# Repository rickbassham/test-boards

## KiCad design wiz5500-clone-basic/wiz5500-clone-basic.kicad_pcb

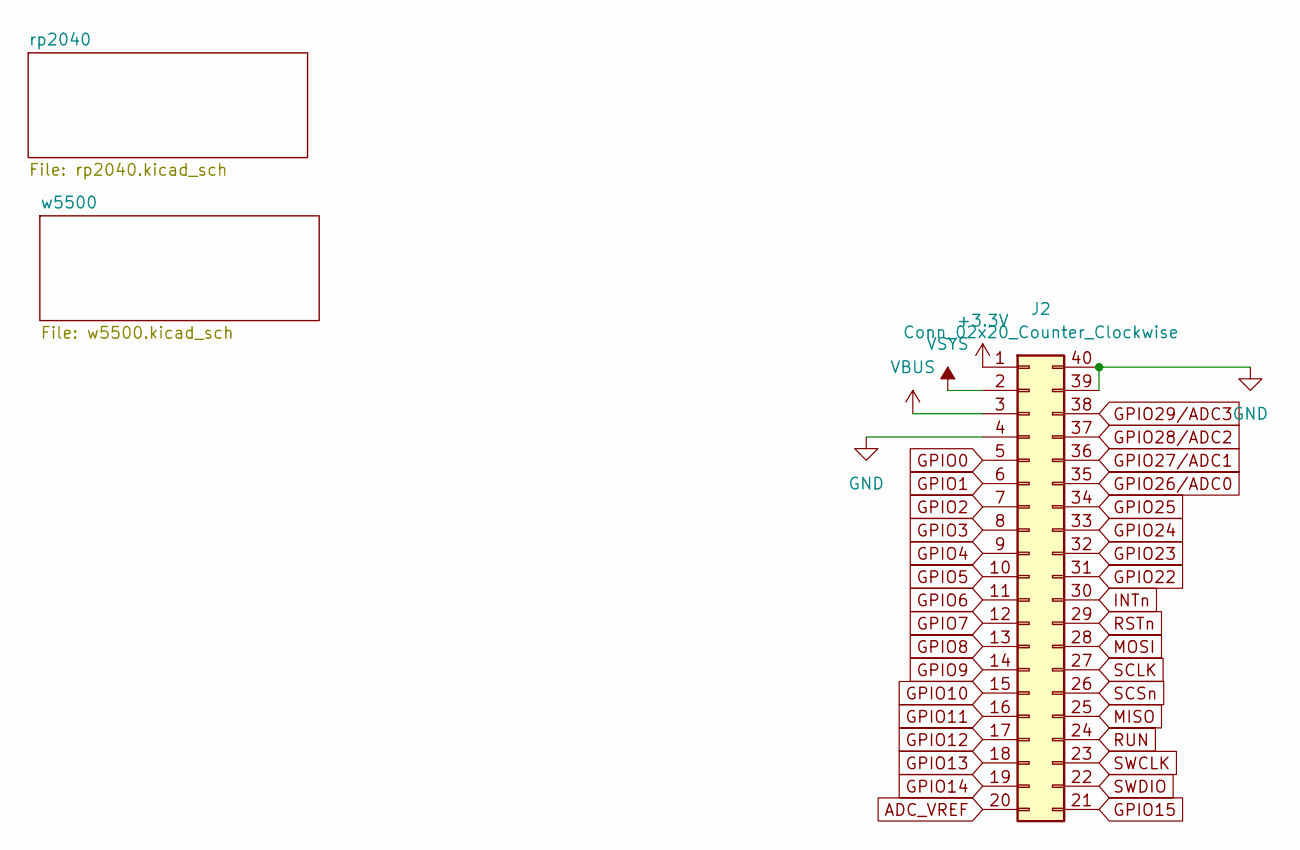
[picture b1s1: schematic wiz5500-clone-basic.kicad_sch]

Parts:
J2: Conn_02x20_Counter_Clockwise; PinHeader_2x20_P2.54mm_Vertical

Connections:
+3V3: J2.1; also elsewhere on the board
ADC_VREF: J2.20; also elsewhere on the board
GND: J2.4, J2.39, J2.40; also elsewhere on the board
GPIO0: J2.5; also elsewhere on the board
GPIO1: J2.6; also elsewhere on the board
GPIO2: J2.7; also elsewhere on the board
GPIO3: J2.8; also elsewhere on the board
GPIO4: J2.9; also elsewhere on the board
GPIO5: J2.10; also elsewhere on the board
GPIO6: J2.11; also elsewhere on the board
GPIO7: J2.12; also elsewhere on the board
GPIO8: J2.13; also elsewhere on the board
GPIO9: J2.14; also elsewhere on the board
GPIO10: J2.15; also elsewhere on the board
GPIO11: J2.16; also elsewhere on the board
GPIO12: J2.17; also elsewhere on the board
GPIO13: J2.18; also elsewhere on the board
GPIO14: J2.19; also elsewhere on the board
GPIO15: J2.21; also elsewhere on the board
GPIO22: J2.31; also elsewhere on the board
GPIO23: J2.32; also elsewhere on the board
GPIO24: J2.33; also elsewhere on the board
GPIO25: J2.34; also elsewhere on the board
GPIO26/ADC0: J2.35; also elsewhere on the board
GPIO27/ADC1: J2.36; also elsewhere on the board
GPIO28/ADC2: J2.37; also elsewhere on the board
GPIO29/ADC3: J2.38; also elsewhere on the board
INTn: J2.30; also elsewhere on the board
MISO: J2.25; also elsewhere on the board
MOSI: J2.28; also elsewhere on the board
RSTn: J2.29; also elsewhere on the board
RUN: J2.24; also elsewhere on the board
SCLK: J2.27; also elsewhere on the board
SCSn: J2.26; also elsewhere on the board
SWCLK: J2.23; also elsewhere on the board
SWDIO: J2.22; also elsewhere on the board
VBUS: J2.3; also elsewhere on the board
VSYS: J2.2; also elsewhere on the board

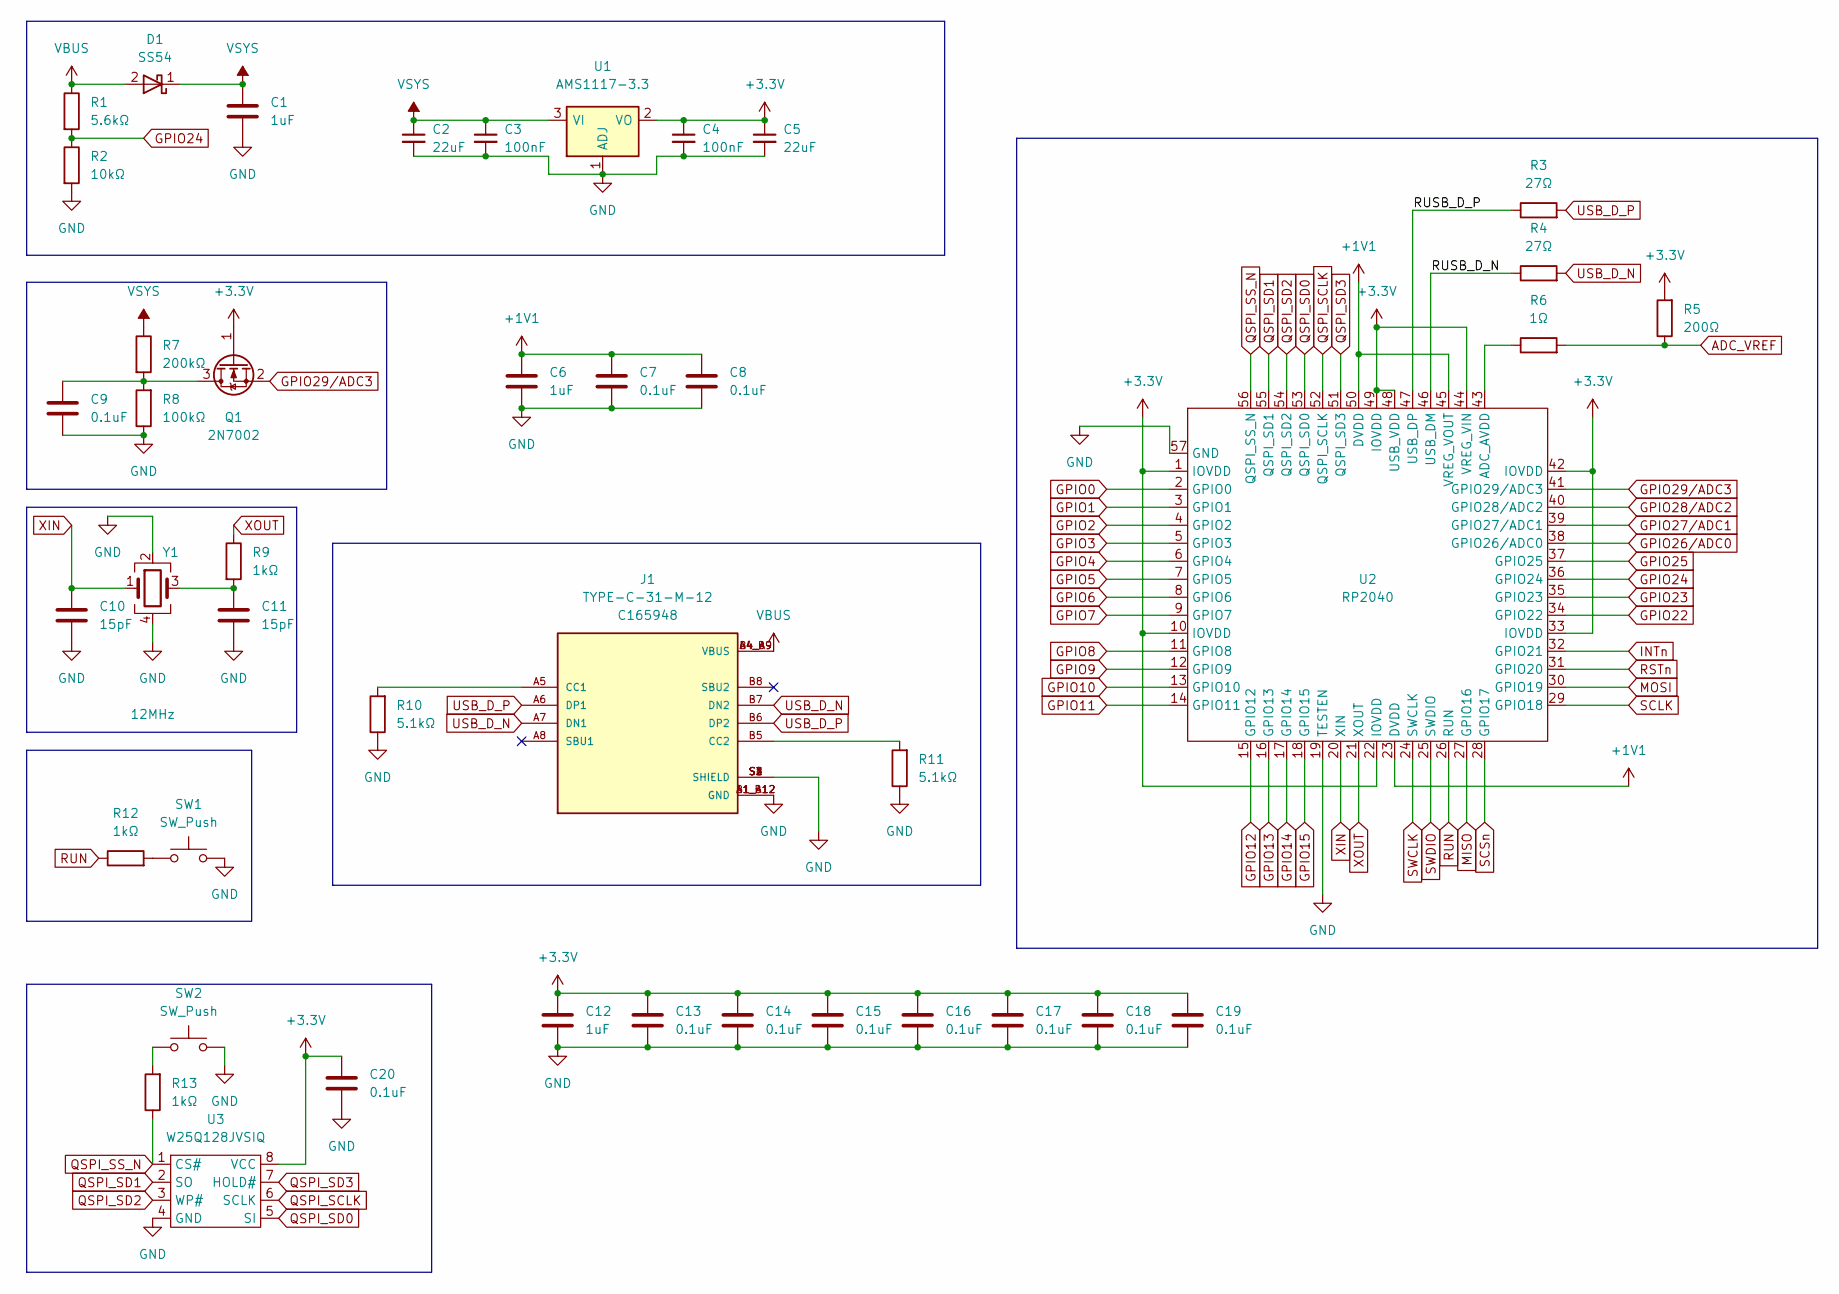
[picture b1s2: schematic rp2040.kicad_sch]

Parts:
C1, C6, C12: 1uF; C_0402_1005Metric; LCSC C52923
C2, C5: 22uF; C_0805_2012Metric; LCSC C45783
C3, C4: 100nF; C_0402_1005Metric; LCSC C307331
C7, C8, C9, C13, C14, C15, C16, C17, C18, C19, C20: 0.1uF; C_0402_1005Metric; LCSC C1525
C10, C11: 15pF; C_0402_1005Metric; LCSC C1548
D1: SS54; D_SMA; LCSC C22452
J1: TYPE-C-31-M-12; HRO_TYPE-C-31-M-12; LCSC C165948
Q1: 2N7002; SOT-23; LCSC C8545
R1: 5.6kΩ; R_0402_1005Metric; LCSC C25908
R2: 10kΩ; R_0402_1005Metric; LCSC C25744
R3, R4: 27Ω; R_0603_1608Metric; LCSC C25190
R5: 200Ω; R_0402_1005Metric; LCSC C25087
R6: 1Ω; R_0402_1005Metric; LCSC C25086
R7: 200kΩ; R_0402_1005Metric; LCSC C25764
R8: 100kΩ; R_0402_1005Metric; LCSC C25741
R9, R12, R13: 1kΩ; R_0402_1005Metric; LCSC C11702
R10, R11: 5.1kΩ; R_0402_1005Metric; LCSC C25905
SW1, SW2: SW_Push; SW_TS-1187A-B-A-B; LCSC C318884
U1: AMS1117-3.3; SOT-223-3_TabPin2; LCSC C6186
U2: RP2040; LCSC C2040
U3: W25Q128JVSIQ; SOIC-8_5.23x5.23mm_P1.27mm; LCSC C97521
Y1: 12MHz; Crystal_SMD_3225-4Pin_3.2x2.5mm; LCSC C9002

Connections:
+1V1: C6.1, C7.1, C8.1, U2.23 (DVDD), U2.45 (VREG_VOUT), U2.50 (DVDD)
+3V3: C4.1, C5.1, C12.1, C13.1, C14.1, C15.1, C16.1, C17.1, C18.1, C19.1, C20.1, Q1.1 (G), R5.2, U1.2 (VO), U2.1 (IOVDD), U2.10 (IOVDD), U2.22 (IOVDD), U2.33 (IOVDD), U2.42 (IOVDD), U2.44 (VREG_VIN), U2.48 (USB_VDD), U2.49 (IOVDD), U3.8 (VCC); also elsewhere on the board
/rp2040/RUSB_D_N: R4.1, U2.46 (USB_DM)
/rp2040/RUSB_D_P: R3.1, U2.47 (USB_DP)
ADC_VREF: R5.1, R6.2; also elsewhere on the board
GND: C1.2, C2.2, C3.2, C4.2, C5.2, C6.2, C7.2, C8.2, C9.2, C10.2, C11.2, C12.2, C13.2, C14.2, C15.2, C16.2, C17.2, C18.2, C19.2, C20.2, J1.A1_B12 (GND), J1.B1_A12 (GND), J1.S1 (SHIELD), J1.S2 (SHIELD), J1.S3 (SHIELD), J1.S4 (SHIELD), R2.2, R8.1, R10.1, R11.1, SW1.2, SW2.2, U1.1 (ADJ), U2.19 (TESTEN), U2.57 (GND), U3.4 (GND), Y1.2, Y1.4; also elsewhere on the board
GPIO0: U2.2 (GPIO0); also elsewhere on the board
GPIO1: U2.3 (GPIO1); also elsewhere on the board
GPIO2: U2.4 (GPIO2); also elsewhere on the board
GPIO3: U2.5 (GPIO3); also elsewhere on the board
GPIO4: U2.6 (GPIO4); also elsewhere on the board
GPIO5: U2.7 (GPIO5); also elsewhere on the board
GPIO6: U2.8 (GPIO6); also elsewhere on the board
GPIO7: U2.9 (GPIO7); also elsewhere on the board
GPIO8: U2.11 (GPIO8); also elsewhere on the board
GPIO9: U2.12 (GPIO9); also elsewhere on the board
GPIO10: U2.13 (GPIO10); also elsewhere on the board
GPIO11: U2.14 (GPIO11); also elsewhere on the board
GPIO12: U2.15 (GPIO12); also elsewhere on the board
GPIO13: U2.16 (GPIO13); also elsewhere on the board
GPIO14: U2.17 (GPIO14); also elsewhere on the board
GPIO15: U2.18 (GPIO15); also elsewhere on the board
GPIO22: U2.34 (GPIO22); also elsewhere on the board
GPIO23: U2.35 (GPIO23); also elsewhere on the board
GPIO24: R1.2, R2.1, U2.36 (GPIO24); also elsewhere on the board
GPIO25: U2.37 (GPIO25); also elsewhere on the board
GPIO26/ADC0: U2.38 (GPIO26/ADC0); also elsewhere on the board
GPIO27/ADC1: U2.39 (GPIO27/ADC1); also elsewhere on the board
GPIO28/ADC2: U2.40 (GPIO28/ADC2); also elsewhere on the board
GPIO29/ADC3: Q1.2 (S), U2.41 (GPIO29/ADC3); also elsewhere on the board
INTn: U2.32 (GPIO21); also elsewhere on the board
MISO: U2.27 (GPIO16); also elsewhere on the board
MOSI: U2.30 (GPIO19); also elsewhere on the board
unnamed: C9.1, Q1.3 (D), R7.2, R8.2
unnamed: C11.1, R9.2, Y1.3
unnamed: J1.A5 (CC1), R10.2
unnamed: J1.B5 (CC2), R11.2
unnamed: R6.1, U2.43 (ADC_AVDD)
unnamed: R12.2, SW1.1
unnamed: R13.2, SW2.1
QSPI_SCLK: U2.52 (QSPI_SCLK), U3.6 (SCLK)
QSPI_SD0: U2.53 (QSPI_SD0), U3.5 (SI)
QSPI_SD1: U2.55 (QSPI_SD1), U3.2 (SO)
QSPI_SD2: U2.54 (QSPI_SD2), U3.3 (WP#)
QSPI_SD3: U2.51 (QSPI_SD3), U3.7 (HOLD#)
QSPI_SS_N: R13.1, U2.56 (QSPI_SS_N), U3.1 (CS#)
RSTn: U2.31 (GPIO20); also elsewhere on the board
RUN: R12.1, U2.26 (RUN); also elsewhere on the board
SCLK: U2.29 (GPIO18); also elsewhere on the board
SCSn: U2.28 (GPIO17); also elsewhere on the board
SWCLK: U2.24 (SWCLK); also elsewhere on the board
SWDIO: U2.25 (SWDIO); also elsewhere on the board
USB_D_N: J1.A7 (DN1), J1.B7 (DN2), R4.2
USB_D_P: J1.A6 (DP1), J1.B6 (DP2), R3.2
VBUS: D1.2 (A), J1.A4_B9 (VBUS), J1.B4_A9 (VBUS), R1.1; also elsewhere on the board
VSYS: C1.1, C2.1, C3.1, D1.1 (K), R7.1, U1.3 (VI); also elsewhere on the board
XIN: C10.1, U2.20 (XIN), Y1.1
XOUT: R9.1, U2.21 (XOUT)

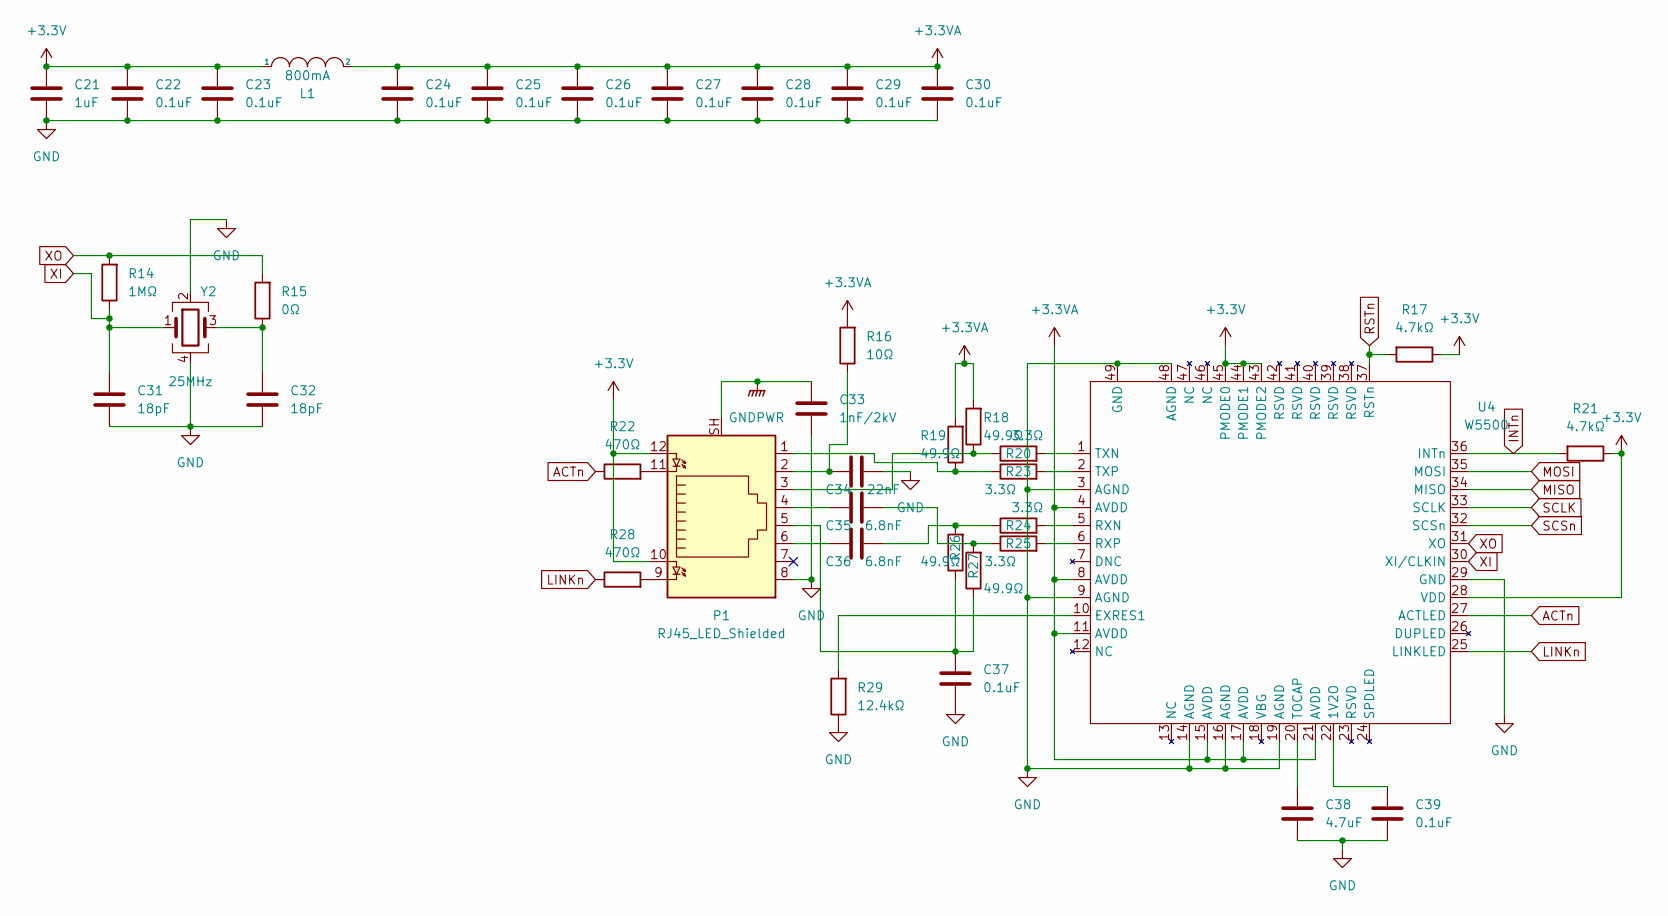
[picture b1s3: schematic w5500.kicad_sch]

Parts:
C21: 1uF; C_0402_1005Metric; LCSC C52923
C22, C23, C24, C25, C26, C27, C28, C29, C30, C37, C39: 0.1uF; C_0402_1005Metric; LCSC C1525
C31, C32: 18pF; C_0402_1005Metric; LCSC C1549
C33: 1nF/2kV; C_1206_3216Metric; LCSC C9196
C34: 22nF; C_0402_1005Metric; LCSC C1532
C35, C36: 6.8nF; C_0402_1005Metric; LCSC C1542
C38: 4.7uF; C_0402_1005Metric; LCSC C23733
L1: 800mA; L_0805_2012Metric; LCSC C1015
P1: RJ45_LED_Shielded; J1B1211CCD; Manufacturer PN J1B1211CCD; LCSC C910371
R14: 1MΩ; R_0402_1005Metric; LCSC C26083
R15: 0Ω; R_0402_1005Metric; LCSC C17168
R16: 10Ω; R_0402_1005Metric; LCSC C25077
R17, R21: 4.7kΩ; R_0402_1005Metric; LCSC C25900
R18, R19, R26, R27: 49.9Ω; R_0402_1005Metric; LCSC C25120
R20, R23, R24, R25: 3.3Ω; R_0402_1005Metric; LCSC C269403
R22, R28: 470Ω; R_0402_1005Metric; LCSC C25117
R29: 12.4kΩ; R_0402_1005Metric; LCSC C11692
U4: W5500; LQFP-48-1EP_7x7mm_P0.5mm_EP3.6x3.6mm; LCSC C32843
Y2: 25MHz; Crystal_SMD_3225-4Pin_3.2x2.5mm; LCSC C9006

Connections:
+3.3VA: C24.1, C25.1, C26.1, C27.1, C28.1, C29.1, C30.1, L1.2, R16.2, R18.2, R19.2, U4.4 (AVDD), U4.8 (AVDD), U4.11 (AVDD), U4.15 (AVDD), U4.17 (AVDD), U4.21 (AVDD)
+3V3: C21.1, C22.1, C23.1, L1.1, P1.10, P1.12, R17.1, R21.1, U4.28 (VDD), U4.43 (PMODE2), U4.44 (PMODE1), U4.45 (PMODE0); also elsewhere on the board
ACTn: R22.1, U4.27 (ACTLED)
GND: C21.2, C22.2, C23.2, C24.2, C25.2, C26.2, C27.2, C28.2, C29.2, C30.2, C31.2, C32.2, C33.2, C34.2, C37.2, C38.2, C39.2, P1.8, R29.1, U4.3 (AGND), U4.9 (AGND), U4.14 (AGND), U4.16 (AGND), U4.19 (AGND), U4.29 (GND), U4.48 (AGND), U4.49 (GND), Y2.2, Y2.4; also elsewhere on the board
GNDPWR: C33.1, P1.SH
INTn: R21.2, U4.36 (INTn); also elsewhere on the board
LINKn: R28.1, U4.25 (LINKLED)
MISO: U4.34 (MISO); also elsewhere on the board
MOSI: U4.35 (MOSI); also elsewhere on the board
unnamed: C32.1, R15.1, Y2.3
unnamed: C34.1, P1.2, R16.1
unnamed: C35.1, P1.4
unnamed: C35.2, R25.1, R27.2
unnamed: C36.1, P1.6
unnamed: C36.2, R24.1, R26.2
unnamed: C37.1, P1.5, R26.1, R27.1
unnamed: C38.1, U4.20 (TOCAP)
unnamed: C39.1, U4.22 (1V2O)
unnamed: P1.1, R19.1, R23.1
unnamed: P1.3, R18.1, R20.1
unnamed: P1.9, R28.2
unnamed: P1.11, R22.2
unnamed: R20.2, U4.1 (TXN)
unnamed: R23.2, U4.2 (TXP)
unnamed: R24.2, U4.5 (RXN)
unnamed: R25.2, U4.6 (RXP)
unnamed: R29.2, U4.10 (EXRES1)
RSTn: R17.2, U4.37 (RSTn); also elsewhere on the board
SCLK: U4.33 (SCLK); also elsewhere on the board
SCSn: U4.32 (SCSn); also elsewhere on the board
XI: C31.1, R14.1, U4.30 (XI/CLKIN), Y2.1
XO: R14.2, R15.2, U4.31 (XO)

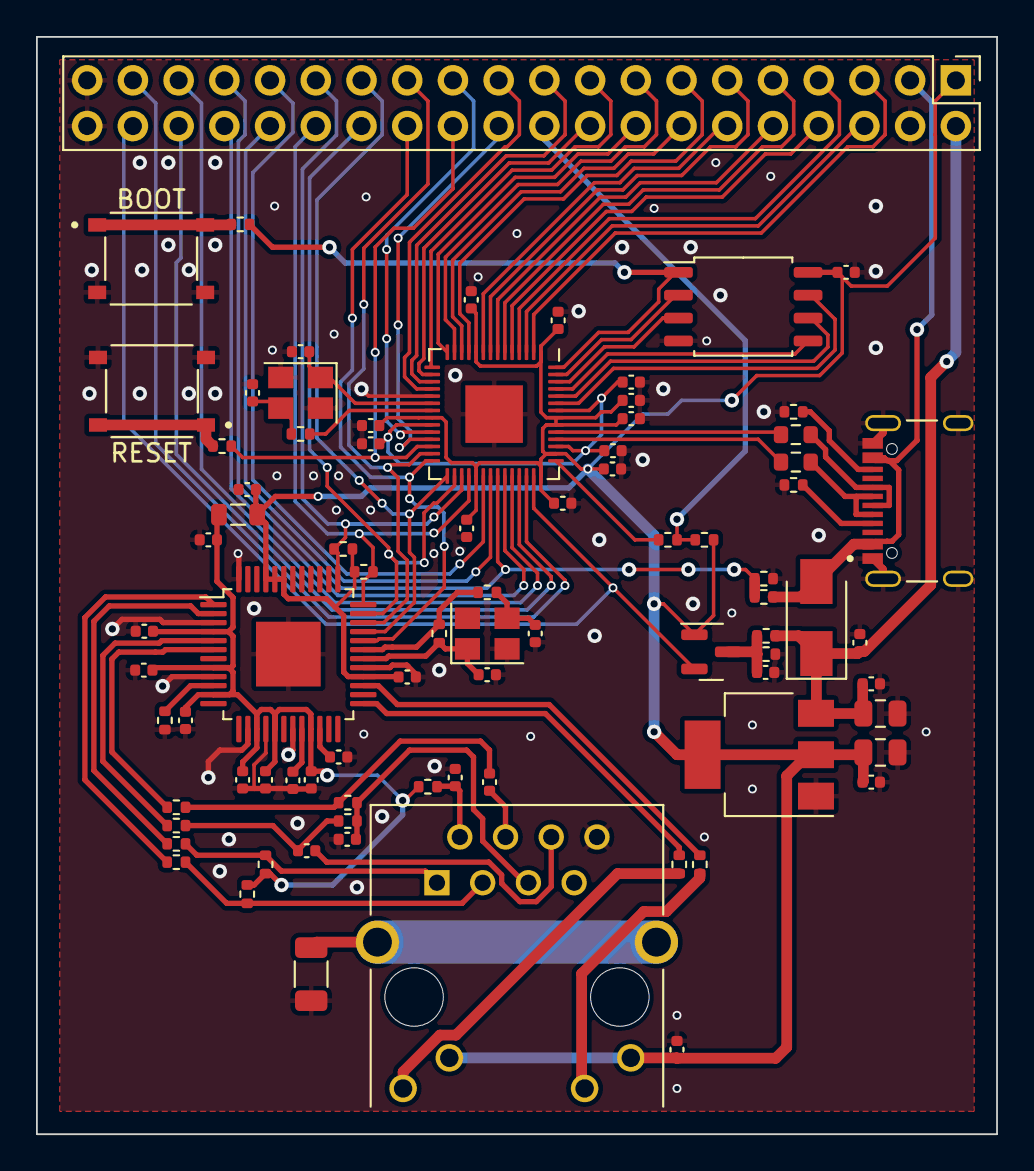
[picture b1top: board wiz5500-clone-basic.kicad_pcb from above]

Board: 2 copper layers, 53.3 x 61.0 mm, 82 parts (0 on the bottom side), 82 nets.

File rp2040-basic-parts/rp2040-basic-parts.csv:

"Designator","JLCPCB Part #","Comment","Footprint"
"C1, C6, C12, ","C52923","1uF","Capacitor_SMD:C_0402_1005Metric"
"C2, C5, ","C45783","22uF","Capacitor_SMD:C_0805_2012Metric"
"C3, C4, ","C307331","100nF","Capacitor_SMD:C_0402_1005Metric"
"C7, C8, C9, C13, C14, C15, C16, C17, C18, C19, C20, ","C1525","0.1uF","Capacitor_SMD:C_0402_1005Metric"
"C10, C11, ","C1548","15pF","Capacitor_SMD:C_0402_1005Metric"
"D1, ","C22452","SS54","Diode_SMD:D_SMA"
"J1, ","C165948","TYPE-C-31-M-12","01-rickbassham:HRO_TYPE-C-31-M-12"
"J2, J3, ","","Conn_01x20","Connector_PinHeader_2.54mm:PinHeader_1x20_P2.54mm_Vertical"
"JP1, ","","Boot_Mode","Connector_PinHeader_2.54mm:PinHeader_1x03_P2.54mm_Vertical"
"Q1, ","C8545","2N7002","Package_TO_SOT_SMD:SOT-23"
"R1, ","C25908","5.6kΩ","Resistor_SMD:R_0402_1005Metric"
"R2, ","C25744","10kΩ","Resistor_SMD:R_0402_1005Metric"
"R3, R4, ","C25190","27Ω","Resistor_SMD:R_0603_1608Metric"
"R5, ","C25087","200Ω","Resistor_SMD:R_0402_1005Metric"
"R6, ","C25086","1Ω","Resistor_SMD:R_0402_1005Metric"
"R7, ","C25764","200kΩ","Resistor_SMD:R_0402_1005Metric"
"R8, ","C25741","100kΩ","Resistor_SMD:R_0402_1005Metric"
"R9, R10, R11, ","C11702","1kΩ","Resistor_SMD:R_0402_1005Metric"
"R12, R13, ","","5.1kΩ","Resistor_SMD:R_0402_1005Metric"
"R14, ","","1MΩ","Resistor_SMD:R_0402_1005Metric"
"SW1, ","C318884","SW_Push","01-rickbassham:SW_TS-1187A-B-A-B"
"U1, ","C6186","AMS1117-3.3","Package_TO_SOT_SMD:SOT-223-3_TabPin2"
"U2, ","C9002","X322512MSB4SI","Crystal:Crystal_SMD_3225-4Pin_3.2x2.5mm"
"U3, ","C2040","RP2040","01-rickbassham:RP2040"
"U4, ","C97521","W25Q128JVSIQ","Package_SO:SOIC-8_3.9x4.9mm_P1.27mm"

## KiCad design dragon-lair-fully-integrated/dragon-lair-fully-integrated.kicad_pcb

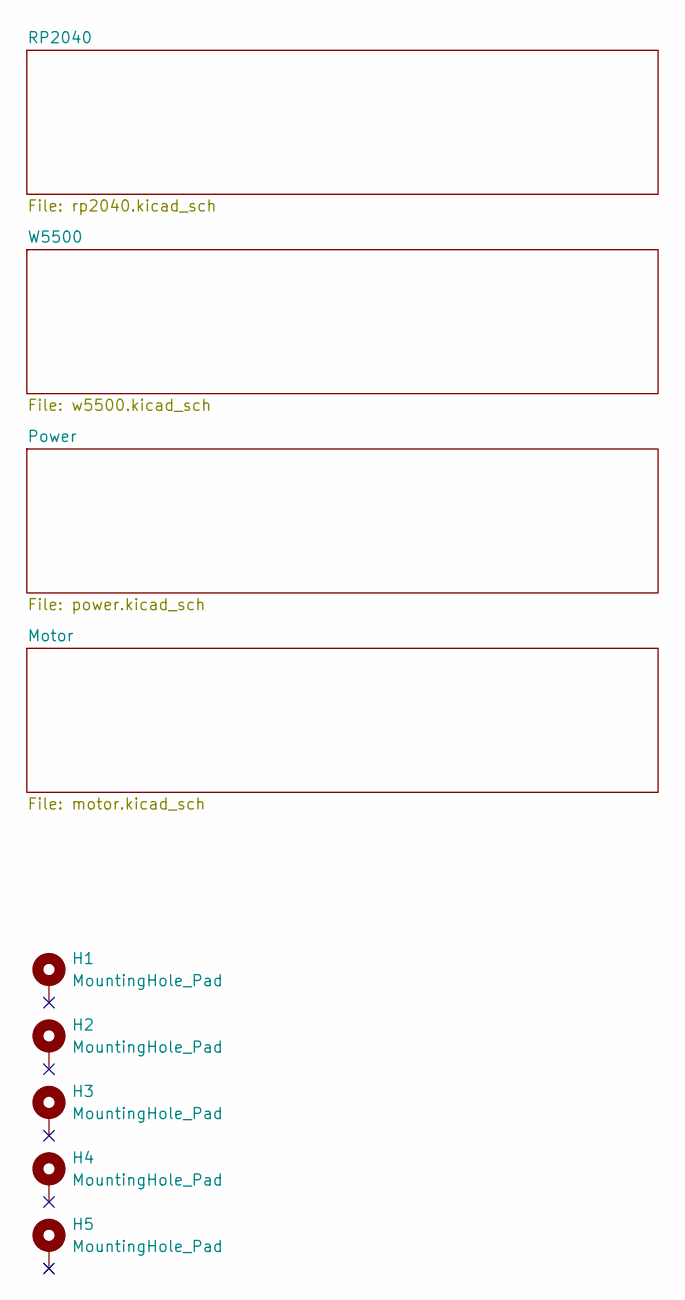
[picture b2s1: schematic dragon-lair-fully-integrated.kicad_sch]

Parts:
H1, H2, H3, H4, H5: MountingHole_Pad; MountingHole_3.2mm_M3_DIN965_Pad

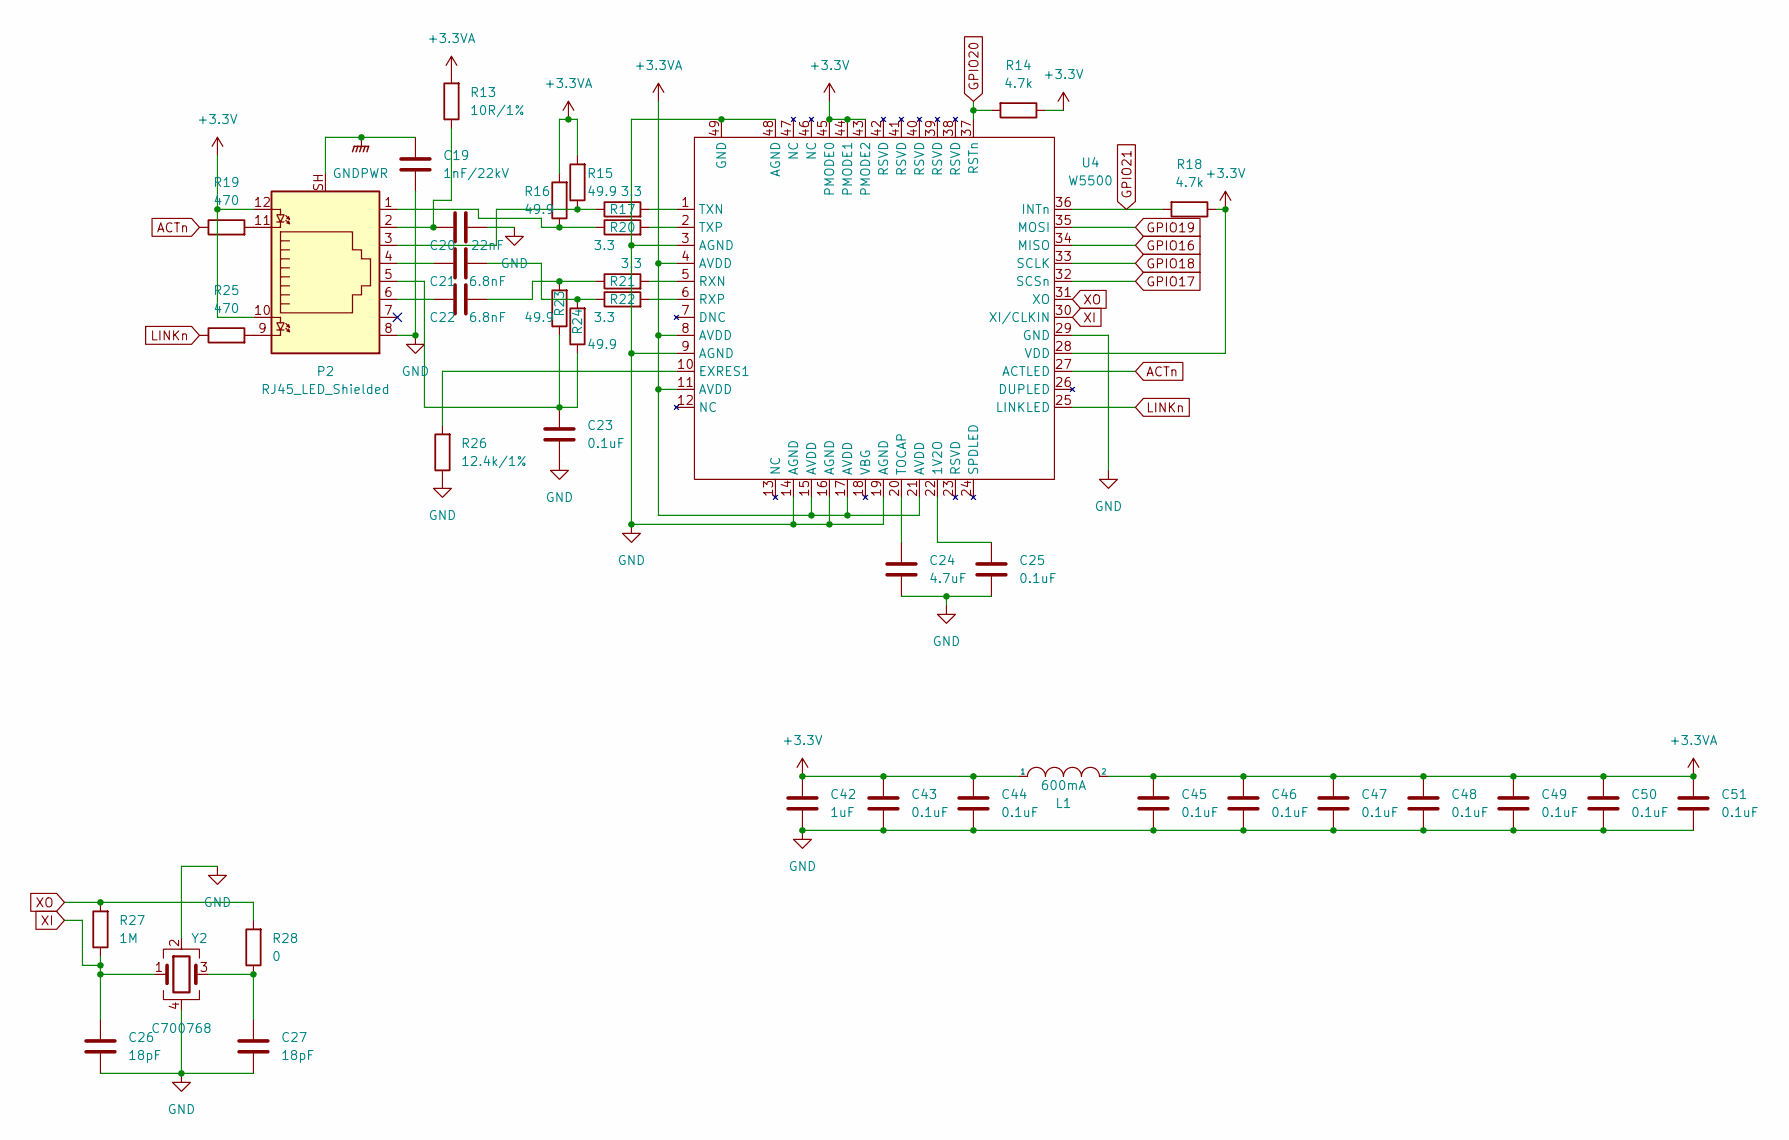
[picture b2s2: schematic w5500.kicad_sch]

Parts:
C19: 1nF/22kV; C_1812_4532Metric; LCSC C304032
C20: 22nF; C_0402_1005Metric; LCSC C1532
C21, C22: 6.8nF; C_0402_1005Metric; LCSC C1542
C23, C25, C43, C44, C45, C46, C47, C48, C49, C50, C51: 0.1uF; C_0402_1005Metric; LCSC C1525
C24: 4.7uF; C_0402_1005Metric; LCSC C23733
C26, C27: 18pF; C_0402_1005Metric; LCSC C1549
C42: 1uF; C_0402_1005Metric; LCSC C52923
L1: 600mA; L_0603_1608Metric; LCSC C280478
P2: RJ45_LED_Shielded; J1B1211CCD; Manufacturer PN J1B1211CCD; LCSC C910371
R13: 10R/1%; R_0402_1005Metric; LCSC C25077
R14, R18: 4.7k; R_0402_1005Metric; LCSC C25900
R15, R16, R23, R24: 49.9; R_0402_1005Metric; LCSC C25120
R17, R20, R21, R22: 3.3; R_0402_1005Metric; LCSC C270612
R19, R25: 470; R_0402_1005Metric; LCSC C25117
R26: 12.4k/1%; R_0402_1005Metric; LCSC C11692
R27: 1M; R_0402_1005Metric; LCSC C26083
R28: 0; R_0402_1005Metric; LCSC C17168
U4: W5500; LQFP-48-1EP_7x7mm_P0.5mm_EP3.6x3.6mm; LCSC C32843
Y2: C700768; Crystal_SMD_3225-4Pin_3.2x2.5mm; LCSC C700768

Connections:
+3.3VA: C45.1, C46.1, C47.1, C48.1, C49.1, C50.1, C51.1, L1.2, R13.2, R15.2, R16.2, U4.4 (AVDD), U4.8 (AVDD), U4.11 (AVDD), U4.15 (AVDD), U4.17 (AVDD), U4.21 (AVDD)
+3V3: C42.1, C43.1, C44.1, L1.1, P2.10, P2.12, R14.1, R18.1, U4.28 (VDD), U4.43 (PMODE2), U4.44 (PMODE1), U4.45 (PMODE0); also elsewhere on the board
ACTn: R19.1, U4.27 (ACTLED)
GND: C19.2, C20.2, C23.2, C24.2, C25.2, C26.2, C27.2, C42.2, C43.2, C44.2, C45.2, C46.2, C47.2, C48.2, C49.2, C50.2, C51.2, P2.8, R26.1, U4.3 (AGND), U4.9 (AGND), U4.14 (AGND), U4.16 (AGND), U4.19 (AGND), U4.29 (GND), U4.48 (AGND), U4.49 (GND), Y2.2, Y2.4; also elsewhere on the board
GNDPWR: C19.1, P2.SH
GPIO16: U4.34 (MISO); also elsewhere on the board
GPIO17: U4.32 (SCSn); also elsewhere on the board
GPIO18: U4.33 (SCLK); also elsewhere on the board
GPIO19: U4.35 (MOSI); also elsewhere on the board
GPIO20: R14.2, U4.37 (RSTn); also elsewhere on the board
GPIO21: R18.2, U4.36 (INTn); also elsewhere on the board
LINKn: R25.1, U4.25 (LINKLED)
unnamed: C20.1, P2.2, R13.1
unnamed: C21.1, P2.4
unnamed: C21.2, R22.1, R24.2
unnamed: C22.1, P2.6
unnamed: C22.2, R21.1, R23.2
unnamed: C23.1, P2.5, R23.1, R24.1
unnamed: C24.1, U4.20 (TOCAP)
unnamed: C25.1, U4.22 (1V2O)
unnamed: C27.1, R28.1, Y2.3
unnamed: P2.1, R16.1, R20.1
unnamed: P2.3, R15.1, R17.1
unnamed: P2.9, R25.2
unnamed: P2.11, R19.2
unnamed: R17.2, U4.1 (TXN)
unnamed: R20.2, U4.2 (TXP)
unnamed: R21.2, U4.5 (RXN)
unnamed: R22.2, U4.6 (RXP)
unnamed: R26.2, U4.10 (EXRES1)
XI: C26.1, R27.1, U4.30 (XI/CLKIN), Y2.1
XO: R27.2, R28.2, U4.31 (XO)

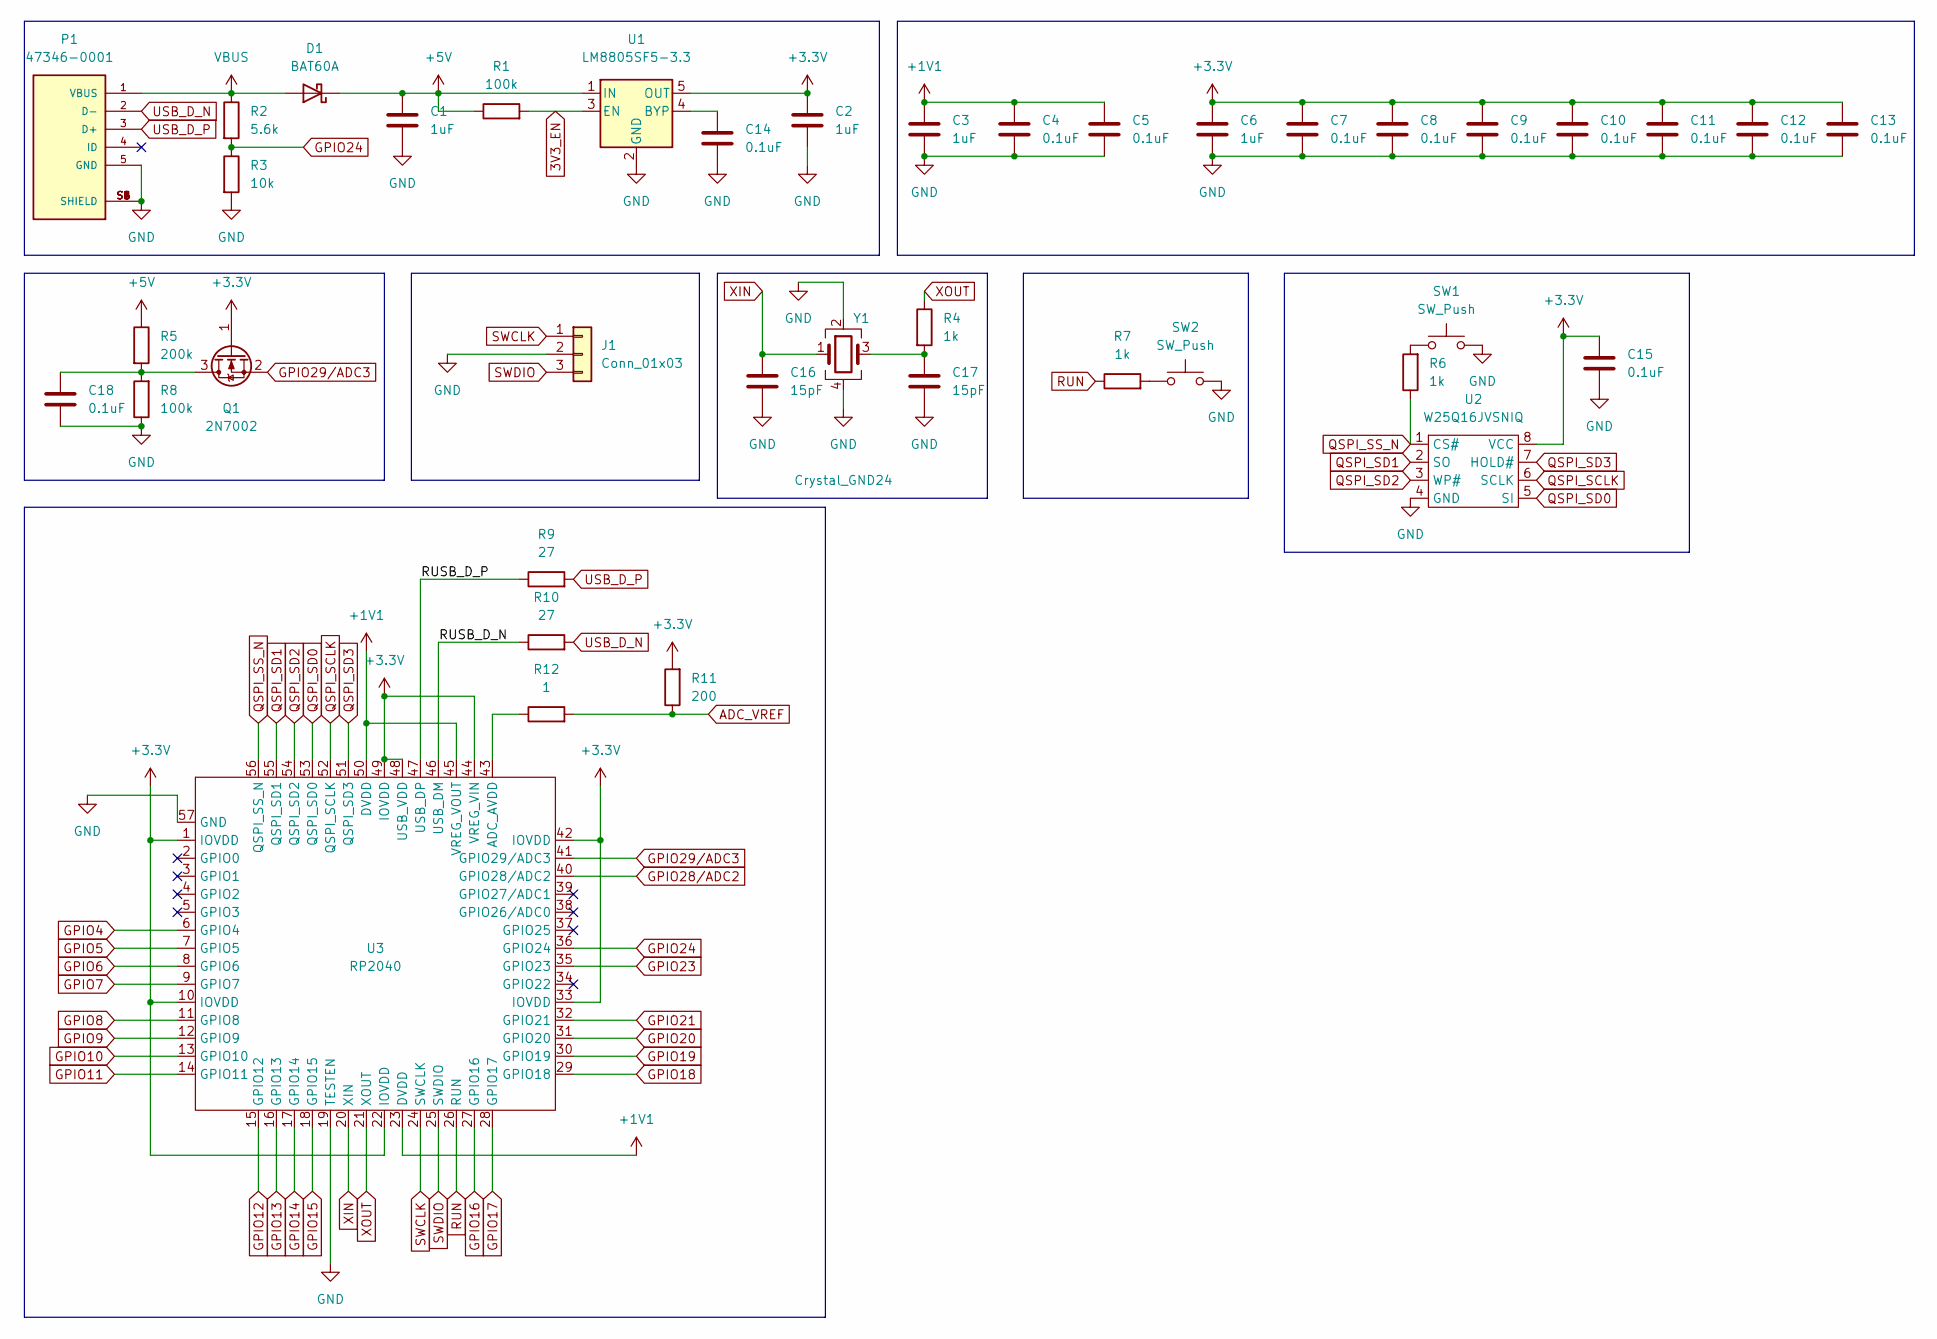
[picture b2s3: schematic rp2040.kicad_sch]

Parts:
C1, C2, C3, C6: 1uF; C_0402_1005Metric; LCSC C52923
C4, C5, C7, C8, C9, C10, C11, C12, C13, C14, C15, C18: 0.1uF; C_0402_1005Metric; LCSC C1525
C16, C17: 15pF; C_0402_1005Metric; LCSC C1548
D1: BAT60A; D_SOD-323; Manufacturer PN BAT60AE6327HTSA1; LCSC C520634
J1: Conn_01x03; PinHeader_1x03_P2.54mm_Vertical
P1: 47346-0001; MOLEX_47346-0001; LCSC C132560
Q1: 2N7002; SOT-23; LCSC C8545
R1, R8: 100k; R_0402_1005Metric; LCSC C25741
R2: 5.6k; R_0402_1005Metric; LCSC C25908
R3: 10k; R_0402_1005Metric; LCSC C25744
R4, R6, R7: 1k; R_0402_1005Metric; LCSC C11702
R5: 200k; R_0402_1005Metric; LCSC C25764
R9, R10: 27; R_0603_1608Metric; LCSC C25190
R11: 200; R_0402_1005Metric; LCSC C25087
R12: 1; R_0402_1005Metric; LCSC C25086
SW1, SW2: SW_Push; SW_TS-1187A-B-A-B; LCSC C318884
U1: LM8805SF5-3.3; SOT-23-5; LCSC C126077
U2: W25Q16JVSNIQ; SOIC-8_3.9x4.9mm_P1.27mm; LCSC C115407
U3: RP2040; LCSC C2040
Y1: Crystal_GND24; Crystal_SMD_3225-4Pin_3.2x2.5mm; LCSC C133334

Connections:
3V3_EN: R1.2, U1.3 (EN)
+1V1: C3.1, C4.1, C5.1, U3.23 (DVDD), U3.45 (VREG_VOUT), U3.50 (DVDD)
+3V3: C2.1, C6.1, C7.1, C8.1, C9.1, C10.1, C11.1, C12.1, C13.1, C15.1, Q1.1 (G), R11.2, U1.5 (OUT), U2.8 (VCC), U3.1 (IOVDD), U3.10 (IOVDD), U3.22 (IOVDD), U3.33 (IOVDD), U3.42 (IOVDD), U3.44 (VREG_VIN), U3.48 (USB_VDD), U3.49 (IOVDD); also elsewhere on the board
+5V: C1.1, D1.1 (K), R1.1, R5.1, U1.1 (IN); also elsewhere on the board
/RP2040/RUSB_D_N: R10.1, U3.46 (USB_DM)
/RP2040/RUSB_D_P: R9.1, U3.47 (USB_DP)
ADC_VREF: R11.1, R12.2; also elsewhere on the board
GND: C1.2, C2.2, C3.2, C4.2, C5.2, C6.2, C7.2, C8.2, C9.2, C10.2, C11.2, C12.2, C13.2, C14.2, C15.2, C16.2, C17.2, C18.2, J1.2, P1.5 (GND), P1.S1 (SHIELD), P1.S2 (SHIELD), P1.S3 (SHIELD), P1.S4 (SHIELD), P1.S5 (SHIELD), P1.S6 (SHIELD), R3.2, R8.1, SW1.2, SW2.2, U1.2 (GND), U2.4 (GND), U3.19 (TESTEN), U3.57 (GND), Y1.2, Y1.4; also elsewhere on the board
GPIO4: U3.6 (GPIO4); also elsewhere on the board
GPIO5: U3.7 (GPIO5); also elsewhere on the board
GPIO6: U3.8 (GPIO6); also elsewhere on the board
GPIO7: U3.9 (GPIO7); also elsewhere on the board
GPIO8: U3.11 (GPIO8); also elsewhere on the board
GPIO9: U3.12 (GPIO9); also elsewhere on the board
GPIO10: U3.13 (GPIO10); also elsewhere on the board
GPIO11: U3.14 (GPIO11); also elsewhere on the board
GPIO12: U3.15 (GPIO12); also elsewhere on the board
GPIO13: U3.16 (GPIO13); also elsewhere on the board
GPIO14: U3.17 (GPIO14); also elsewhere on the board
GPIO15: U3.18 (GPIO15); also elsewhere on the board
GPIO16: U3.27 (GPIO16); also elsewhere on the board
GPIO17: U3.28 (GPIO17); also elsewhere on the board
GPIO18: U3.29 (GPIO18); also elsewhere on the board
GPIO19: U3.30 (GPIO19); also elsewhere on the board
GPIO20: U3.31 (GPIO20); also elsewhere on the board
GPIO21: U3.32 (GPIO21); also elsewhere on the board
GPIO23: U3.35 (GPIO23); also elsewhere on the board
GPIO24: R2.2, R3.1, U3.36 (GPIO24)
GPIO28/ADC2: U3.40 (GPIO28/ADC2); also elsewhere on the board
GPIO29/ADC3: Q1.2 (S), U3.41 (GPIO29/ADC3)
unnamed: C14.1, U1.4 (BYP)
unnamed: C17.1, R4.2, Y1.3
unnamed: C18.1, Q1.3 (D), R5.2, R8.2
unnamed: R6.2, SW1.1
unnamed: R7.2, SW2.1
unnamed: R12.1, U3.43 (ADC_AVDD)
QSPI_SCLK: U2.6 (SCLK), U3.52 (QSPI_SCLK)
QSPI_SD0: U2.5 (SI), U3.53 (QSPI_SD0)
QSPI_SD1: U2.2 (SO), U3.55 (QSPI_SD1)
QSPI_SD2: U2.3 (WP#), U3.54 (QSPI_SD2)
QSPI_SD3: U2.7 (HOLD#), U3.51 (QSPI_SD3)
QSPI_SS_N: R6.1, U2.1 (CS#), U3.56 (QSPI_SS_N)
RUN: R7.1, U3.26 (RUN)
SWCLK: J1.1, U3.24 (SWCLK)
SWDIO: J1.3, U3.25 (SWDIO)
USB_D_N: P1.2 (D-), R10.2
USB_D_P: P1.3 (D+), R9.2
VBUS: D1.2 (A), P1.1 (VBUS), R2.1
XIN: C16.1, U3.20 (XIN), Y1.1
XOUT: R4.1, U3.21 (XOUT)
